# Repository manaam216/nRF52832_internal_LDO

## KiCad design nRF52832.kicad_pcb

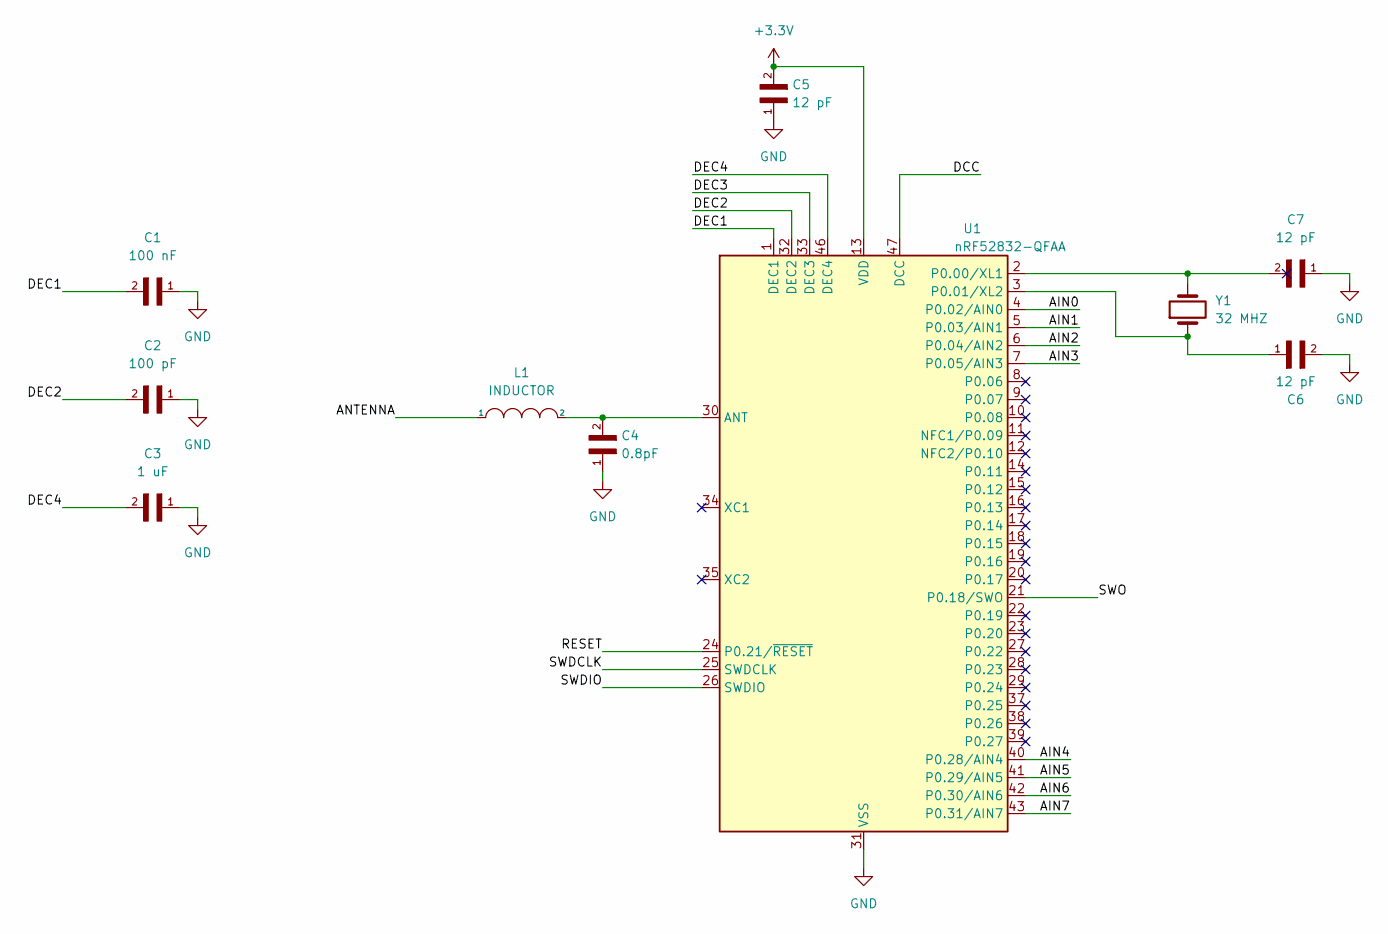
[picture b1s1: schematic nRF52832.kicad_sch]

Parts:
C1: 100 nF; C_0402_1005Metric
C2: 100 pF; C_0402_1005Metric
C3: 1 uF; C_0402_1005Metric
C4: 0.8pF; C_0402_1005Metric
C5, C6, C7: 12 pF; C_0402_1005Metric
L1: INDUCTOR; L_0201_0603Metric
U1: nRF52832-QFAA; QFN-48-1EP_6x6mm_P0.4mm_EP4.6x4.6mm
Y1: 32 MHZ; Oscillator_SMD_EuroQuartz_XO32-4Pin_3.2x2.5mm

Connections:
+3.3V: C5.2, U1.13 (VDD), U1.36 (VDD), U1.48 (VDD)
/AIN0: U1.4 (P0.02/AIN0)
/AIN1: U1.5 (P0.03/AIN1)
/AIN2: U1.6 (P0.04/AIN2)
/AIN3: U1.7 (P0.05/AIN3)
/AIN4: U1.40 (P0.28/AIN4)
/AIN5: U1.41 (P0.29/AIN5)
/AIN6: U1.42 (P0.30/AIN6)
/AIN7: U1.43 (P0.31/AIN7)
/ANTENNA: L1.1
/DCC: U1.47 (DCC)
/DEC1: C1.2, U1.1 (DEC1)
/DEC2: C2.2, U1.32 (DEC2)
/DEC3: U1.33 (DEC3)
/DEC4: C3.2, U1.46 (DEC4)
/RESET: U1.24 (P0.21/~RESET)
/SWDCLK: U1.25 (SWDCLK)
/SWDIO: U1.26 (SWDIO)
/SWO: U1.21 (P0.18/SWO)
GND: C1.1, C2.1, C3.1, C4.1, C5.1, C6.2, C7.1, U1.31 (VSS), U1.45 (VSS), U1.49 (VSS)
unnamed: C6.1, U1.3 (P0.01/XL2), Y1.1
unnamed: C7.2, U1.2 (P0.00/XL1), Y1.2
unnamed: C4.2, L1.2, U1.30 (ANT)

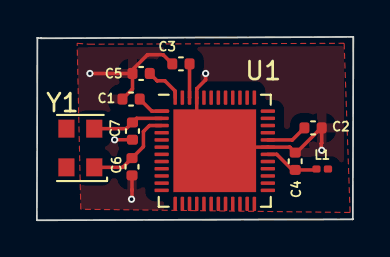
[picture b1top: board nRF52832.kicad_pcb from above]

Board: 2 copper layers, 17.6 x 10.2 mm, 10 parts (0 on the bottom side), 8 nets.

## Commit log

2022-08-29 Add files via upload
    nRF52832 internal LDO setup designed in KiCAD
